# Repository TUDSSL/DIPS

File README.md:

# DIPS

This is the official public repository for **DIPS**: **D**ebugger for **I**ntermittently-**P**owered **S**ystems. The repository consists of all components that make DIPS:
- [Hardware](https://github.com/TUDSSL/DIPS/tree/master/hardware)
- [Debugger Firmware](https://github.com/TUDSSL/DIPS/tree/master/int-debugger-firmware)
- [Emulator Firmware](https://github.com/TUDSSL/DIPS/tree/master/int-debugger-emulator)
- [Emulator Host (GUI)](https://github.com/TUDSSL/DIPS/tree/master/int-debugger-emulator-host)
- [DIPS Console](https://github.com/TUDSSL/DIPS/tree/master/int-debugger-console)

## Project Overview
### Rationale
Intermittently-Powered or Battery-Free systems are low-powered embedded systems that experience frequent power failures. In recent years intermittently-powered systems have been explored excessively by the research community, but there was no good way of debugging these systems. DIPS aims to address this challenge. 

### Debugging Intermittently-Powered Systems
Common debuggers, like the [J-link](https://www.segger.com/products/debug-probes/j-link/), are perfect for debugging continuously-powered systems but will lose connection on a power failure when debugging intermittently-powered systems, making it useless for debugging battery-free systems. On top of that, intermittently-powered systems come with their own set of challenges by introducing new architectures like checkpointing. DIPS allows for continuous debugging despite power failures by reconnecting automatically and restoring the debugging state (Breakpoints) to the device under test. Scripts supplement the functionality of DIPS, allowing for automated tests of memory and peripheral consistency.

### Features:
DIPS integrates a fully featured emulator with close integration with an onboard hardware debugger. It can power devices under test through various modes and features current measurement capability. A key feature is the ability to pause emulation during debugger interaction, such as breakpoints. The emulator supports the following modes:
- Constant Voltage
- Sawtooth
- Square
- Triangle
- Virtual Buck-Boost (Allows for replaying energy harvesting traces to the device under test)
- Passive mode (Only takes over powering the device when prompted during debugging, requires passive debugging mode **mon passive_mode enable**)

The hardware debugger supports, through the associated console application, supports the following features:

- **energy_guards** energy-neutral code sections  where the emulator pauses
- **energy_breakpoints** that only trigger if the voltage is lower than the specified threshold
- **dips_mem_check** memory state consistency verification script, configured in **dips_testing.json**
- **dips_peripheral_check** peripheral state consistency verification script, configured in **dips_testing.json**
- Printing (**DIPS_PRINTF**), asserts (**DIPS_ASSERT**) and manually attaching (**DIPS_ATTACH**) through a simple C interface
- Passive operation (**wait_connect**) where the debugger only connects when prompted through a pin. 

### Hardware

#### Hardware Debugger
The hardware design of the debugger centers around a STM32F103RET MCU (A) and is based on the [Black Magic Debug Probe](https://github.com/blackmagic-debug/blackmagic). It is able to communicate with the energy emulator through SPI. The MCU interfaces with the DUT through SWD/JTAG or SBW (E), I/O interrupt pins and acts as a UART-USB bridge (D). To translate the signals to the DUT voltage, first, the DUT voltage is buffered using a low input bias current buffer amplifier OPA192. Next, all the interfaces with the DUT are level shifted by level translators (C) using the buffered DUT
voltage. The debugger connects to the PC with USB (B). 

#### Energy Emulator 
Central to the energy emulator is the low-noise TPS7A87 (I) linear regulator. The regulator generates the adjustable supply rail to the DUT (J). Power consumption by the DUT is measured by two INA186 current sense amplifiers (H). The first amplifier with a 5.6 Ω sense resistor measures large currents without imposing a high burden voltage. The second amplifier with a 1000 Ω sense resistor measures low currents and is able to be bypassed at large currents preventing high burden voltages. Two analog switches allow for quickly disabling the output and discharging the output through a 47 Ω resistor. The emulator is controlled by a STM32F373 MCU (G). With its on-board DAC DIPS is able to adjust the linear regulator and samples the output voltage and the output of the current sense amplifiers (each using one of its dedicated on-board Sigma Delta ADCs). The energy emulator connects to the PC with USB (F)

#### Design files
In the **hardware** folder both the KICAD design files are provided together with a PDF schematic and gerbers.

## Getting Started
This repository has all information to build your own DIPS. Below we describe building and executing the complete repository of DIPS, including hardware, debugger software, emulator software and both emulator and console applications.

### Building the Debugger Firmware
The hardware debugger firmware is based on the [Black Magic Probe](https://github.com/blackmagic-debug/blackmagic) and can be found in the [/int-debugger-firmware](https://github.com/TUDSSL/DIPS/tree/master/int-debugger-firmware) folder

#### Build Process
After cloning the repository one can compile the firmware in two ways, first is by running it as a [PlatformIO](https://platformio.org/) project or by building it from scratch using the provided cmake files running the following section:

```
$ cd int-debugger-firmware
$ pio run
```

After building, you can upload the firmware to the MCU using your favourite flashing method whilst powering the platform using USB.

#### Last Tested Software Versions
This software was build successfully with these software versions:

- CMake version 3.26.3 
- arm-none-eabi-gcc version 13.1.0 
- arm-none-eabi-newlib version 4.3.0.20230120
- arm-none-eabi-binutils version 2.40 
- PlatformIO version 6.1.7

### The Emulator Firmware
The emulator firmware is located in the [/int-debugger-emulator](https://github.com/TUDSSL/DIPS/tree/master/int-debugger-emulator) folder

#### Build Process
After cloning the repository the emulator can be compiled and build by running the enclosed cmake commands:

```
$ cd int-debugger-emulator
$ mkdir build
$ cd build
$ cmake ..
$ make
```

After building, you can upload the firmware to the MCU using your favourite flashing method whilst powering the platform using USB.

#### Note on the Emulator Firmware
The firmware is based upon the [FreeRTOS](https://www.freertos.org/) framework, allowing real-time switching of tasks required for the emulator.

#### Last Tested Software Versions
This software was build successfully with these software versions:

- CMake version 3.26.3 
- arm-none-eabi-gcc version 13.1.0 
- arm-none-eabi-newlib version 4.3.0.20230120
- arm-none-eabi-binutils version 2.40
- Protobuf version 21.12

### Building the Emulator Host Software
The next part of software runs on the host PC and is used for communicating with the hardware emulator. The sofware can be found in the [/int-debugger-emulator-host](https://github.com/TUDSSL/DIPS/tree/master/int-debugger-emulator-host) folder.

#### Build Process
After cloning the repository the emulator host application can be compiled and build by running the following commands:

```
$ cd int-debugger-emulator-host
$ cmake .
$ make
```

#### Last Tested Software Versions
This software was build successfully with these software versions:

- [QT](https://www.qt.io/) version 5.15.9
- [HighFive](https://github.com/BlueBrain/HighFive) commit 00dad7172c
- Protobuf version 21.12
- HDF5 version 1.14.1

### The DIPS Console Software
The next part of software also runs on the host PC and is used as a GDB wrapper, allowing the added features of DIPS. The sofware can be found in the [/int-debugger-console](https://github.com/TUDSSL/DIPS/tree/master/int-debugger-console) folder.

#### Setup
Since the DIPS console is a python executable, there is no need for compilation. Install the python libraries mentioned in the `requirements.txt` file and you should be good to go.

#### Last Tested Software Versions
This software was build successfully with these software versions:

- Python version 3.11.3
- Python-pyGDBmi version 0.11.0.0
- Python-pyserial version 3.5
- Python-prompt_toolkit version 3.0.38 
- Python-cmsis_svd version 0.4

#### Execute DIPS Console Application
The DIPS console application can be started by calling the `python3 main.py`, if you have an elf-file binary, you can load this by adding this as extra parameter `python3 main.py firmware.elf`. Other GDB parameters and queries from the command line are avaliable as well.

##### Connecting to DIPS
If you have your DIPS connected over USB you can connect to the hardware by running the `connect` command. The console will automatically search for a DIPS serial connection, establish this connection and connect to the attached device under test. Now one can start debugging intermittenlty-powered systems with DIPS, just like debugging regular powered embedded systems. Manual connection to DIPS is also possible by running the following sequence:

```
(gdb) tar ext /dev/ttyACM0
(gdb) mon s
(gdb) attach 1
```

##### Sample session
After connecting to the DIPS and the device under test, regular arm-none-eabi-gdb commands are availble for use:

```
> python3 main.py example.elf
...<GDB Copyright message>
(gdb) connect
Remote debugging using /dev/ttyACM0
Target voltage: 3.00V
Available Targets:
No. Att Driver
 1      STM32F40x M3/M4
Attaching to program: <code_folder>/example.elf, Remote target
0x800007c in main ()
(gdb) load
Loading section .text, size 0x5868 lma 0x8000000
Loading section .data, size 0x9e0 lma 0x8005868
Loading section .rodata, size 0x254 lma 0x8006248
Start address 0x800007c, load size 25756
Transfer rate: 31 KB/sec, 919 bytes/write.
(gdb) b main
(gdb) c
Breakpoint 1 at 0x80000e8: file <code_folder>/main.c, line 20.
(gdb)
```
## How to Cite This Work

The results of this project have been published in a peer-reviewed academic publication (from which all technical figures in this file originate). Details of the publication are as follows.

* **Authors and the project team:** [Jasper de Winkel](https://www.jasperdewinkel.com/), [Tom Hoefnagel](https://www.linkedin.com/in/tobrec), [Boris Blokland](https://www.linkedin.com/in/boris-blokland-2a0b22138/), [Przemysław Pawełczak](https://www.pawelczak.net/)
* **Publication title:** _DIPS: Debug Intermittently-Powered Systems Like Any Embedded System_
* **Pulication venue:** [Proceedings of ACM SenSys 2022](http://sensys.acm.org/2022/)
* [**Link to publication**](https://doi.org/10.1145/3560905.3568543)

To cite this publication please use the following BiBTeX entry.

```
@inproceedings{dewinkel:sensys:2022:dips,
 author = {de Winkel, Jasper and Hoefnagel, Tom and Blokland, Boris and Pawe\l{}czak, Przemys\l{}aw},
 title = {{DIPS}: Debug Intermittently-Powered Systems Like Any Embedded System},
 booktitle = {Proc. SenSys},
 year = {2022},
 address = {Boston, MA, USA},
 date = nov # " 6--9",
 publisher = {ACM},
 url = {https://doi.org/10.1145/3560905.3568543}
}
```

## Acknowledgments

This research project was supported by [Netherlands Organisation for Scientific Research](https://www.nwo.nl/en), partly funded by the [Dutch Ministry of Economic Affairs and Climate Policy](https://www.government.nl/ministries/ministry-of-economic-affairs-and-climate-policy), through [TTW Perspective program ZERO (P15-01)](https://www.nwo.nl/en/researchprogrammes/perspectief/previous-awards/zero-towards-energy-autonomous-systems-iot) within Project P1.

## Copyright

Copyright (C) 2022 TU Delft Embedded Systems Group/Sustainable Systems Laboratory.

MIT Licence or otherwise specified. See [license](https://github.com/TUDSSL/ENGAGE/blob/master/LICENSE) file for details.

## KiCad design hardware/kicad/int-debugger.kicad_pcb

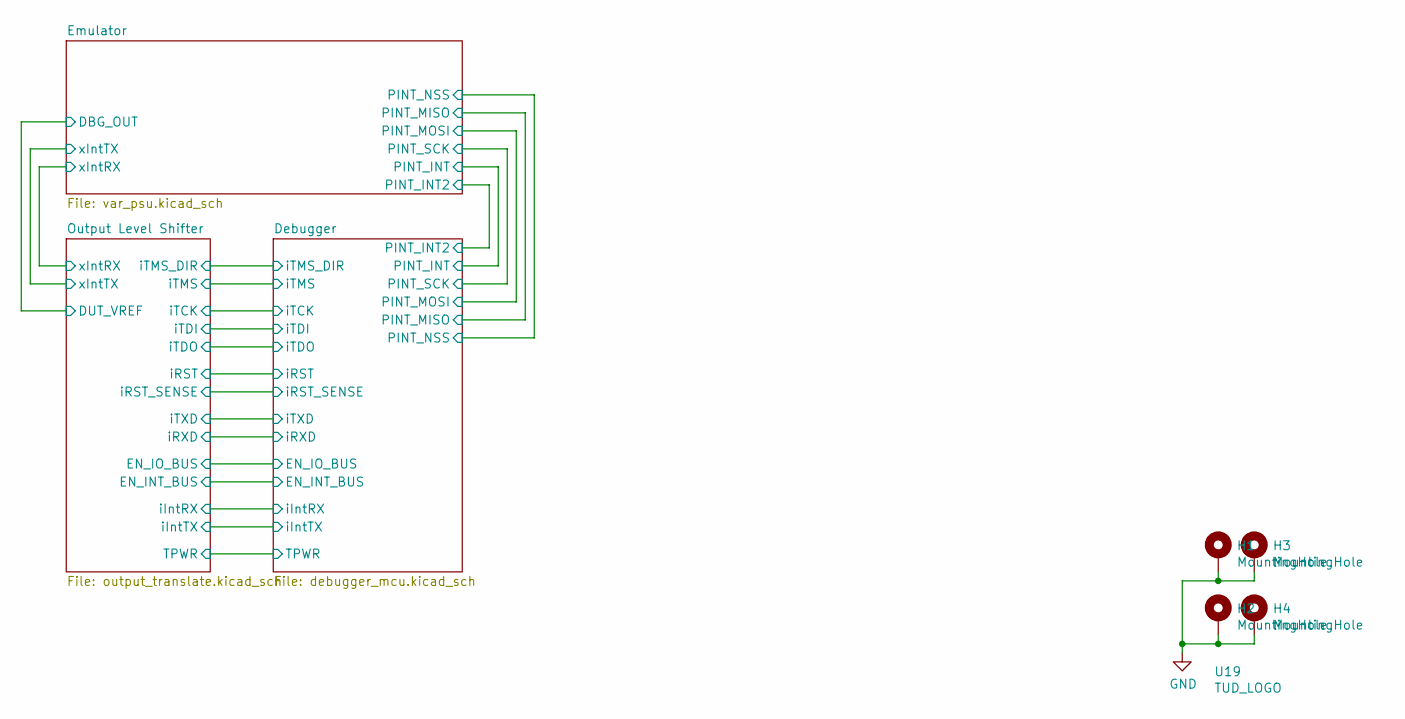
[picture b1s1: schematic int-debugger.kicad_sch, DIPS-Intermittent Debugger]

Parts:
H1, H2, H3, H4: MountingHole; MountingHole_2.2mm_M2_DIN965_Pad_TopBottom
U19: TUD_LOGO; DELFT_LOGO2

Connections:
GND: H1.1, H2.1, H3.1, H4.1; also elsewhere on the board

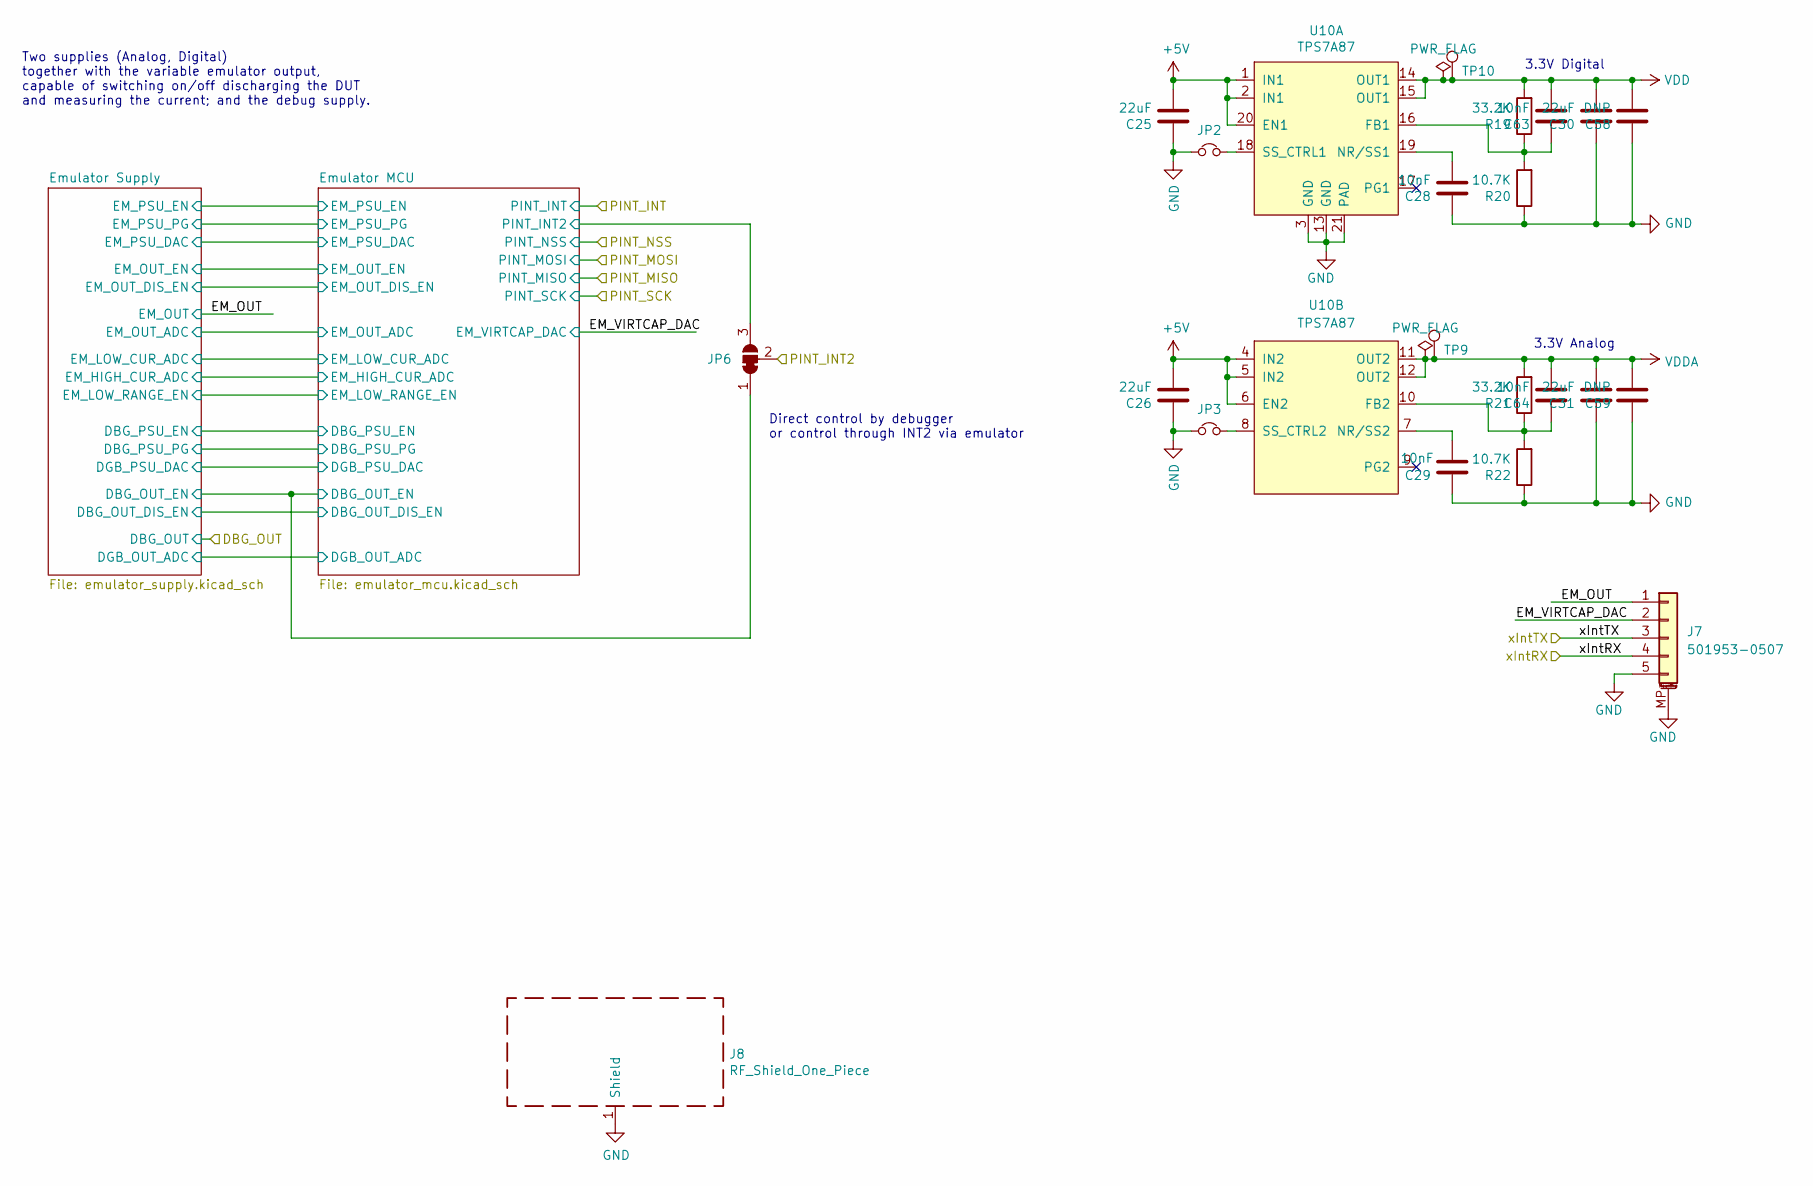
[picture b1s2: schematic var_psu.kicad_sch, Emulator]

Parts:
C25, C26, C30, C31: 22uF; C_0603_1608Metric; MPN GRM188R61A226ME15D
C28, C29, C63, C64: 10nF; C_0603_1608Metric; MPN 06035C103KAT2A
C58, C59: DNP; C_0603_1608Metric
J7: 501953-0507; Molex_Pico-Clasp_501953-0507_1x05-1MP_P1.00mm_Horizontal; MPN 501953-0507
J8: RF_Shield_One_Piece; Laird_Technologies_BMI-S-209-F_29.36x18.50mm; MPN BMI-S-209-F + BMI-S-209-C
JP2, JP3: Jumper_NC_Small; SolderJumper-small-nc
JP6: SolderJumper_3_Bridged12; SolderJumper-3_P1.3mm_Bridged12_Pad1.0x1.5mm
R19, R21: 33.2K; R_0603_1608Metric; MPN RC0603FR-0733K2L
R20, R22: 10.7K; R_0603_1608Metric; MPN RC0603FR-0710K7L
TP9, TP10: TestPoint; TestPoint_Keystone_5000-5004_Miniature
U10: TPS7A87; Texas-WQFN-20

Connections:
+5V: C25.2, C26.2, U10.1 (IN1), U10.2 (IN1), U10.4 (IN2), U10.5 (IN2), U10.6 (EN2), U10.20 (EN1); also elsewhere on the board
/Debugger/PINT_INT2: JP6.2 (C); also elsewhere on the board
/Emulator/EM_OUT: J7.1; also elsewhere on the board
/Emulator/EM_VIRTCAP_DAC: J7.2; also elsewhere on the board
/Emulator/Emulator MCU/DBG_OUT_EN: JP6.1 (A); also elsewhere on the board
/Emulator/Emulator MCU/PINT_INT2: JP6.3 (B); also elsewhere on the board
/Emulator/xIntRX: J7.4; also elsewhere on the board
/Emulator/xIntTX: J7.3; also elsewhere on the board
GND: C25.1, C26.1, C28.1, C29.1, C30.1, C31.1, C58.1, C59.1, J7.5, J7.MP (MountPin), J8.1 (Shield), JP2.1, JP3.1, R20.1, R22.1, U10.3 (GND), U10.13 (GND), U10.21 (PAD); also elsewhere on the board
unnamed: C63.1, R19.1, R20.2, U10.16 (FB1)
unnamed: C28.2, U10.19 (NR/SS1)
unnamed: JP2.2, U10.18 (SS_CTRL1)
unnamed: C64.1, R21.1, R22.2, U10.10 (FB2)
unnamed: C29.2, U10.7 (NR/SS2)
unnamed: JP3.2, U10.8 (SS_CTRL2)
VDD: C30.2, C58.2, C63.2, R19.2, TP10.1, U10.14 (OUT1), U10.15 (OUT1); also elsewhere on the board
VDDA: C31.2, C59.2, C64.2, R21.2, TP9.1, U10.11 (OUT2), U10.12 (OUT2); also elsewhere on the board

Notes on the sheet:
Direct control by debugger or control through INT2 via emulator
3.3V Digital
Two supplies (Analog, Digital) together with the variable emulator output, capable of switching on/off discharging the DUT and measuring the current; and the debug supply.
3.3V Analog

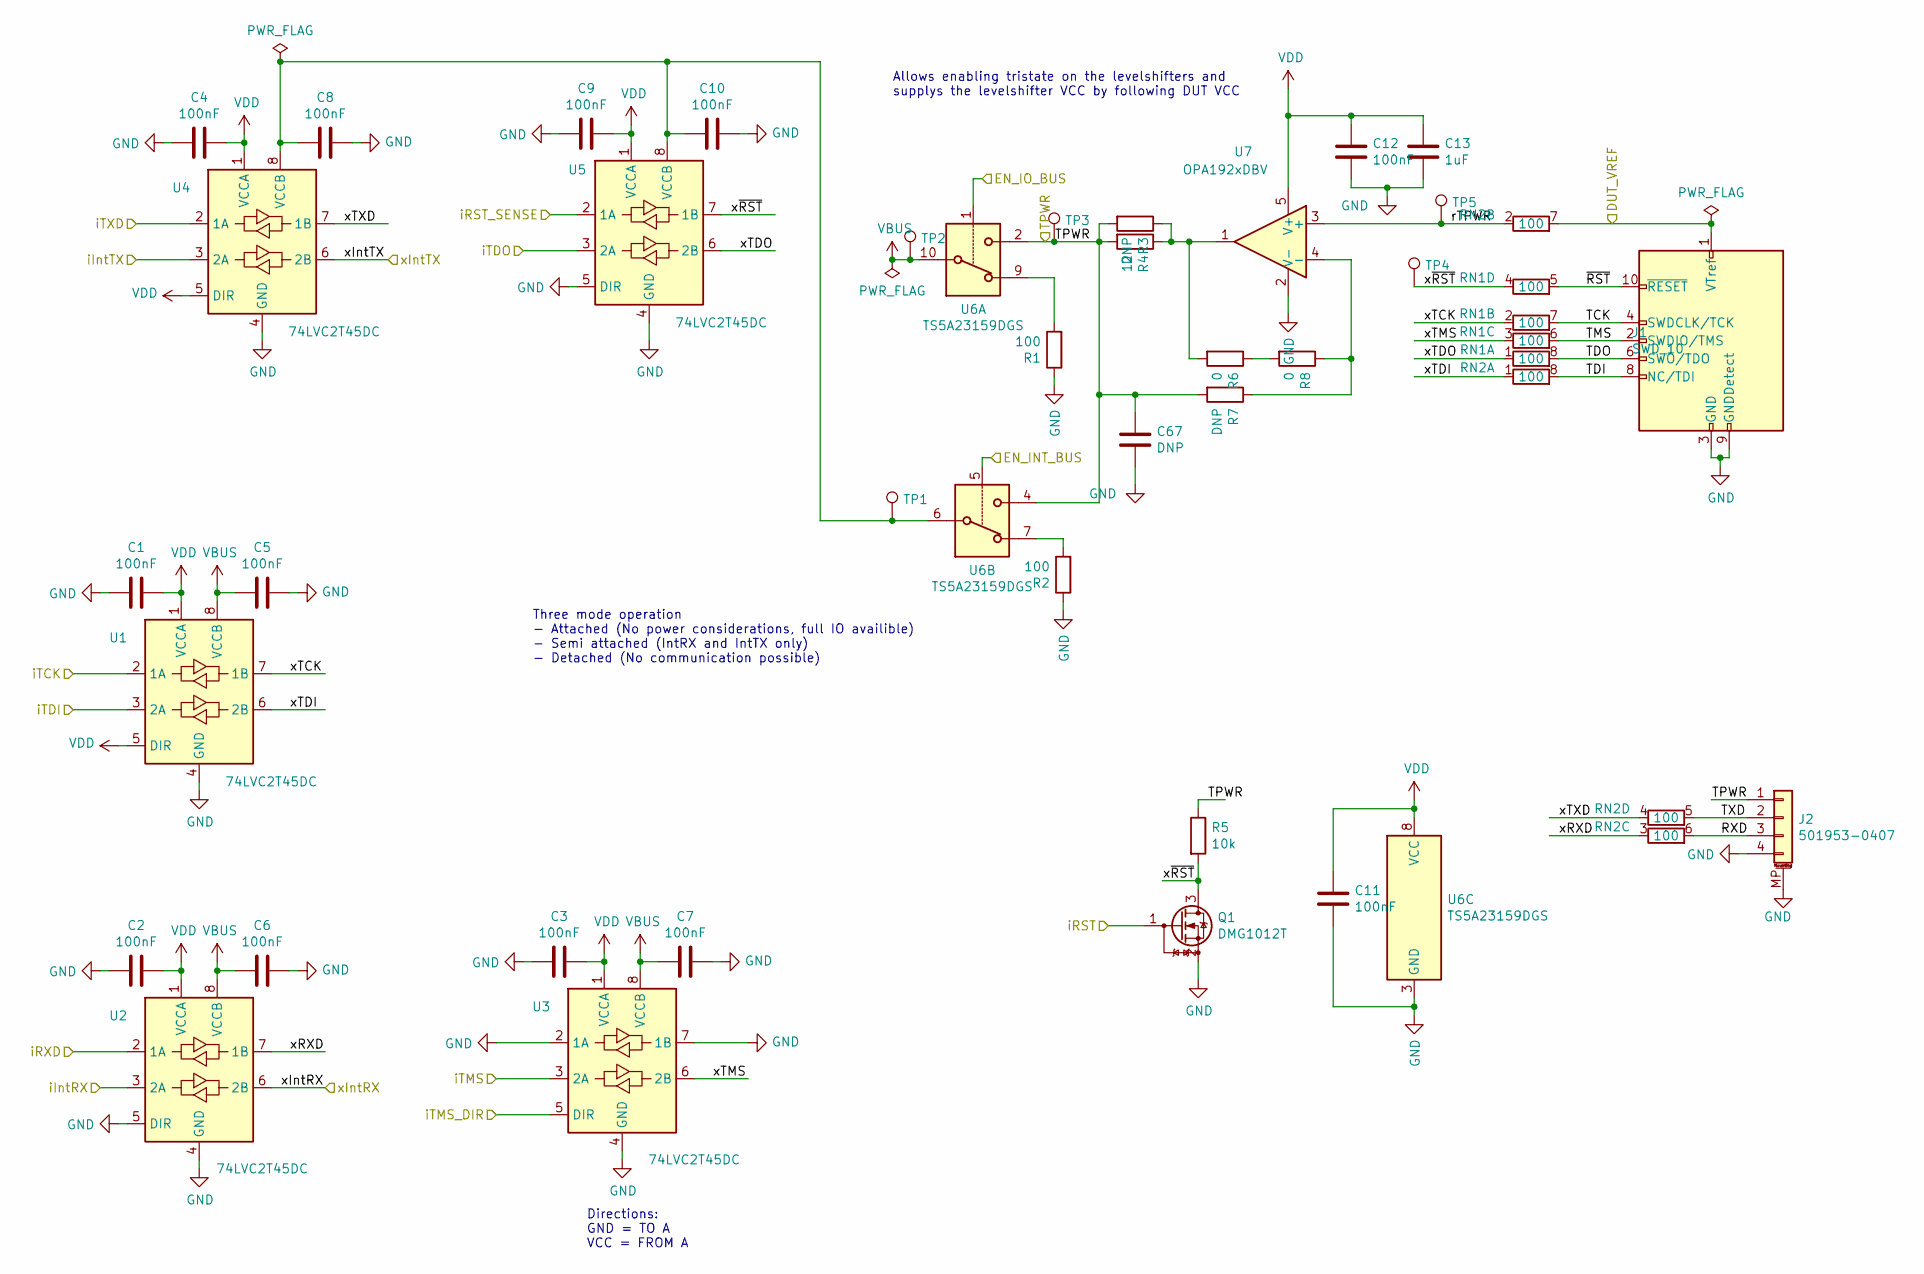
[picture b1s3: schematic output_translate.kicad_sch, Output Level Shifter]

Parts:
C1, C2, C3, C4, C5, C6, C7, C8, C9, C10, C11, C12: 100nF; C_0603_1608Metric; MPN CL10B104KB8NNNC
C13: 1uF; C_0603_1608Metric; MPN TMK107B7105KA-T
C67: DNP; C_0603_1608Metric
J1: SWD_10; FTSH-105-01-F-D-RA-K; MPN FTSH-105-01-F-D-RA-K
J2: 501953-0407; Molex_Pico-Clasp_501953-0407_1x04-1MP_P1.00mm_Horizontal; MPN 501953-0407
Q1: DMG1012T; SOT-523; MPN DMG1012T
R1, R2: 100; R_0603_1608Metric; MPN RC0603FR-07100RL
R3, R7: DNP; R_0603_1608Metric
R4: 12; R_0603_1608Metric; MPN RC0603FR-0712RL
R5: 10k; R_0603_1608Metric; MPN RC0603FR-0710KL
R6, R8: 0; R_0603_1608Metric; MPN RC0603FR-070RL
RN1, RN2: 100; R_Array_Convex_4x1206; MPN YC324-JK-07100RL
TP1, TP2, TP3, TP4, TP5: TestPoint; TestPoint_Keystone_5000-5004_Miniature
U1, U2, U3, U4, U5: 74LVC2T45DC; VSSOP-8_2.3x2mm_P0.5mm; MPN 74LVC2T45DC
U6: TS5A23159DGS; VSSOP-10_3x3mm_P0.5mm; MPN TS5A23159DGS
U7: OPA192xDBV; SOT-23-5; MPN OPA192IDBV

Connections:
/Debugger/EN_INT_BUS: U6.5; also elsewhere on the board
/Debugger/EN_IO_BUS: U6.1; also elsewhere on the board
/Debugger/TPWR: C67.1, J2.1, R3.2, R4.2, R5.1, R7.2, TP3.1, U6.2, U6.4; also elsewhere on the board
/Debugger/iIntRX: U2.3 (2A); also elsewhere on the board
/Debugger/iIntTX: U4.3 (2A); also elsewhere on the board
/Debugger/iRST: Q1.1 (G); also elsewhere on the board
/Debugger/iRST_SENSE: U5.2 (1A); also elsewhere on the board
/Debugger/iRXD: U2.2 (1A); also elsewhere on the board
/Debugger/iTCK: U1.2 (1A); also elsewhere on the board
/Debugger/iTDI: U1.3 (2A); also elsewhere on the board
/Debugger/iTDO: U5.3 (2A); also elsewhere on the board
/Debugger/iTMS: U3.3 (2A); also elsewhere on the board
/Debugger/iTMS_DIR: U3.5 (DIR); also elsewhere on the board
/Debugger/iTXD: U4.2 (1A); also elsewhere on the board
/Emulator/DBG_OUT: J1.1 (VTref), RN2.7 (R2.2); also elsewhere on the board
/Emulator/xIntRX: U2.6 (2B); also elsewhere on the board
/Emulator/xIntTX: U4.6 (2B); also elsewhere on the board
/Output Level Shifter/RXD: J2.3, RN2.6 (R3.2)
/Output Level Shifter/TCK: J1.4 (SWDCLK/TCK), RN1.7 (R2.2)
/Output Level Shifter/TDI: J1.8 (NC/TDI), RN2.8 (R1.2)
/Output Level Shifter/TDO: J1.6 (SWO/TDO), RN1.8 (R1.2)
/Output Level Shifter/TMS: J1.2 (SWDIO/TMS), RN1.6 (R3.2)
/Output Level Shifter/TXD: J2.2, RN2.5 (R4.2)
/Output Level Shifter/rTPWR: RN2.2 (R2.1), TP5.1, U7.3 (+)
/Output Level Shifter/xRXD: RN2.3 (R3.1), U2.7 (1B)
/Output Level Shifter/xTCK: RN1.2 (R2.1), U1.7 (1B)
/Output Level Shifter/xTDI: RN2.1 (R1.1), U1.6 (2B)
/Output Level Shifter/xTDO: RN1.1 (R1.1), U5.6 (2B)
/Output Level Shifter/xTMS: RN1.3 (R3.1), U3.6 (2B)
/Output Level Shifter/xTXD: RN2.4 (R4.1), U4.7 (1B)
/Output Level Shifter/x~RST: Q1.3 (D), R5.2, RN1.4 (R4.1), TP4.1, U5.7 (1B)
/Output Level Shifter/~RST: J1.10 (~RESET), RN1.5 (R4.2)
GND: C1.2, C2.2, C3.2, C4.2, C5.1, C6.1, C7.1, C8.1, C9.2, C10.1, C11.2, C12.2, C13.2, C67.2, J1.3 (GND), J1.5 (GND), J1.9 (GNDDetect), J2.4, J2.MP (MountPin), Q1.2 (S), R1.1, R2.1, U1.4 (GND), U2.4 (GND), U2.5 (DIR), U3.2 (1A), U3.4 (GND), U3.7 (1B), U4.4 (GND), U5.4 (GND), U5.5 (DIR), U6.3 (GND), U7.2 (V-); also elsewhere on the board
unnamed: R1.2, U6.9
unnamed: R2.2, U6.7
unnamed: R3.1, R4.1, R6.2, U7.1
unnamed: R6.1, R8.2
unnamed: C8.2, C10.2, TP1.1, U4.8 (VCCB), U5.8 (VCCB), U6.6
unnamed: R7.1, R8.1, U7.4 (-)
VBUS: C5.2, C6.2, C7.2, TP2.1, U1.8 (VCCB), U2.8 (VCCB), U3.8 (VCCB), U6.10
VDD: C1.1, C2.1, C3.1, C4.1, C9.1, C11.1, C12.1, C13.1, U1.1 (VCCA), U1.5 (DIR), U2.1 (VCCA), U3.1 (VCCA), U4.1 (VCCA), U4.5 (DIR), U5.1 (VCCA), U6.8 (VCC), U7.5 (V+); also elsewhere on the board

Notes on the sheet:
Allows enabling tristate on the levelshifters and supplys the levelshifter VCC by following DUT VCC
Three mode operation - Attached (No power considerations, full IO availible) - Semi attached (IntRX and IntTX only) - Detached (No communication possible)
Directions: GND = TO A VCC = FROM A

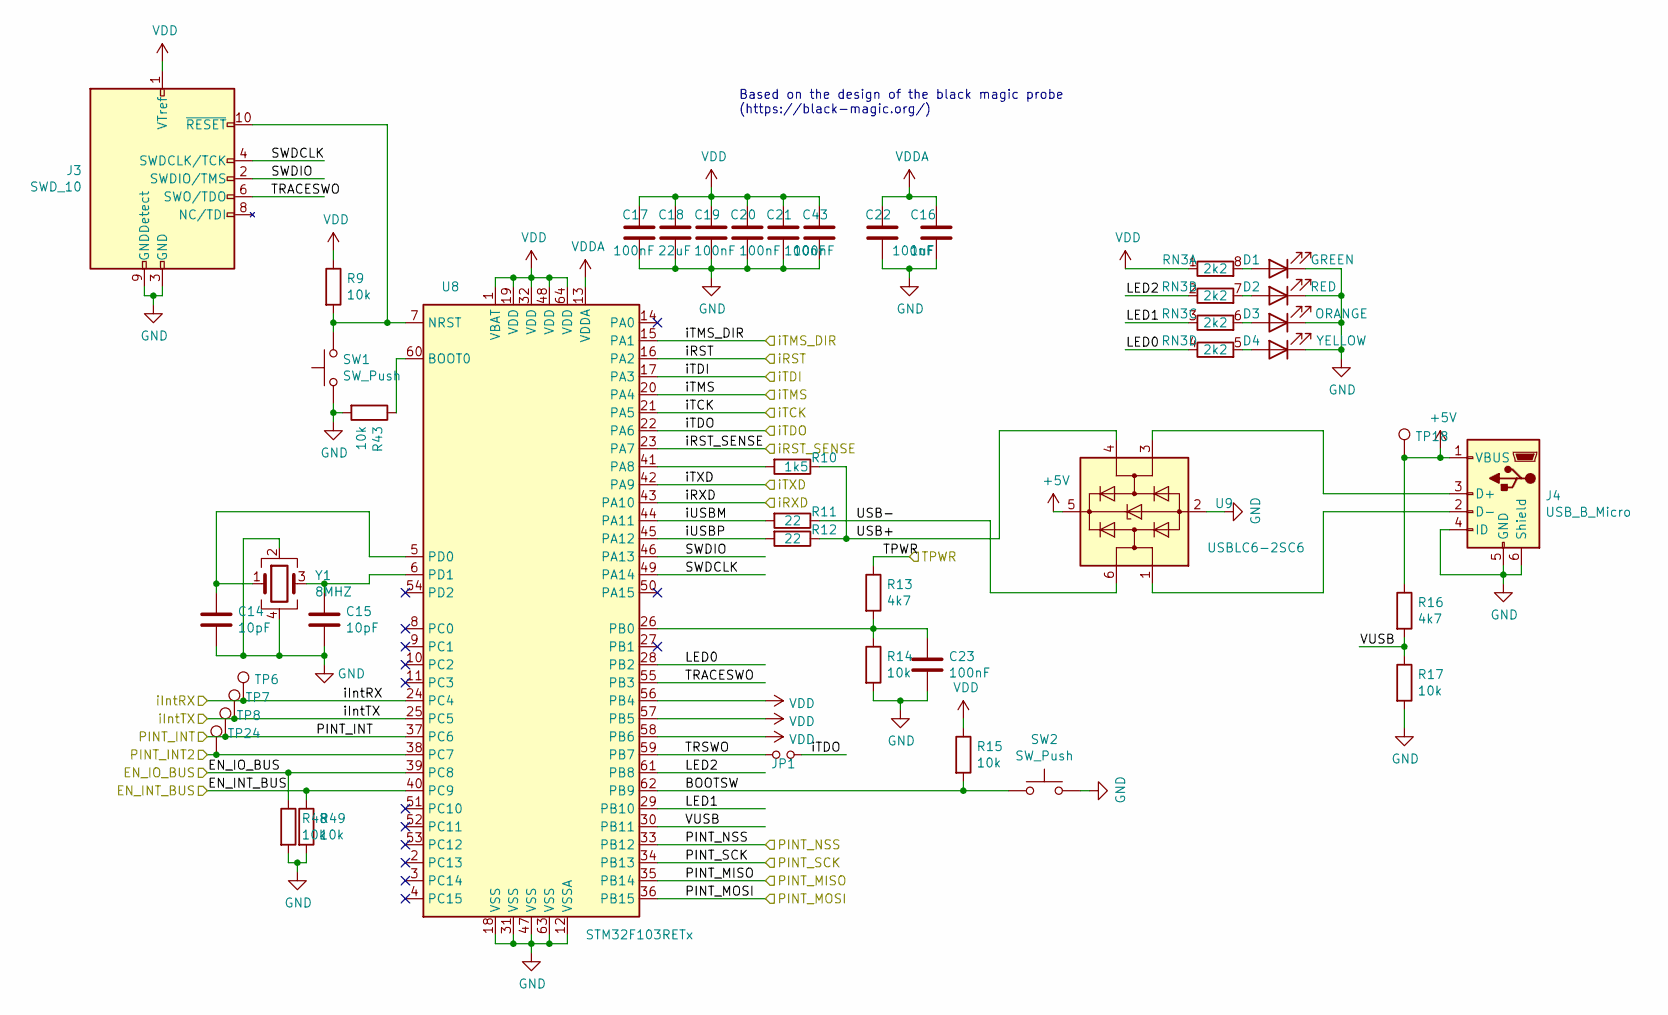
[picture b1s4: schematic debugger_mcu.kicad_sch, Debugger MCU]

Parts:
C14, C15: 10pF; C_0603_1608Metric; MPN CC0603CRNPO9BN100
C16: 1uF; C_0603_1608Metric; MPN TMK107B7105KA-T
C17, C19, C20, C21, C22, C23, C43: 100nF; C_0603_1608Metric; MPN CL10B104KB8NNNC
C18: 22uF; C_0603_1608Metric; MPN GRM188R61A226ME15D
D1: GREEN; LED_0603_1608Metric; MPN LTST-C190KGKT
D2: RED; LED_0603_1608Metric; MPN LTST-C193KRKT-5A
D3: ORANGE; LED_0603_1608Metric; MPN APT1608LSECK/J4-PRV
D4: YELLOW; LED_0603_1608Metric; MPN APTD1608LSYCK/J3-PF
J3: SWD_10; ftsh-105-01-f-dv-k; MPN ftsh-105-01-f-dv-k
J4: USB_B_Micro; USB_Micro-B_Molex-105017-0001; MPN 105017-0001
JP1: Jumper_NO_Small; SolderJumper-small-no-150um
R9, R14, R15, R17, R43, R48, R49: 10k; R_0603_1608Metric; MPN RC0603FR-0710KL
R10: 1k5; R_0603_1608Metric; MPN RC0603FR-071K5L
R11, R12: 22; R_0603_1608Metric; MPN RC0603FR-0722RL
R13, R16: 4k7; R_0603_1608Metric; MPN RC0603FR-074K7L
RN3: 2k2; R_Array_Convex_4x1206; MPN YC324-JK-072K2L
SW1, SW2: SW_Push; SW_SPST_B3U-1000P; MPN B3U-1000P
TP6, TP7, TP8, TP18, TP24: TestPoint; TestPoint_Keystone_5000-5004_Miniature
U8: STM32F103RETx; LQFP-64_10x10mm_P0.5mm; MPN STM32F103RET
U9: USBLC6-2SC6; SOT-23-6; MPN USBLC6-2SC6
Y1: 8MHZ; Crystal_SMD_Abracon_ABM3B-4Pin_5.0x3.2mm; MPN ABM3B-8.000MHZ-10-D-1-G-T

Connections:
+5V: J4.1 (VBUS), R16.1, TP18.1, U9.5 (VBUS); also elsewhere on the board
/Debugger/BOOTSW: R15.2, SW2.1, U8.62 (PB9)
/Debugger/EN_INT_BUS: R49.1, U8.40 (PC9); also elsewhere on the board
/Debugger/EN_IO_BUS: R48.1, U8.39 (PC8); also elsewhere on the board
/Debugger/LED0: RN3.4 (R4.1), U8.28 (PB2)
/Debugger/LED1: RN3.3 (R3.1), U8.29 (PB10)
/Debugger/LED2: RN3.2 (R2.1), U8.61 (PB8)
/Debugger/PINT_INT: TP8.1, U8.37 (PC6); also elsewhere on the board
/Debugger/PINT_INT2: TP24.1, U8.38 (PC7); also elsewhere on the board
/Debugger/PINT_MISO: U8.35 (PB14); also elsewhere on the board
/Debugger/PINT_MOSI: U8.36 (PB15); also elsewhere on the board
/Debugger/PINT_NSS: U8.33 (PB12); also elsewhere on the board
/Debugger/PINT_SCK: U8.34 (PB13); also elsewhere on the board
/Debugger/SWDCLK: J3.4 (SWDCLK/TCK), U8.49 (PA14)
/Debugger/SWDIO: J3.2 (SWDIO/TMS), U8.46 (PA13)
/Debugger/TPWR: R13.1; also elsewhere on the board
/Debugger/TRACESWO: J3.6 (SWO/TDO), U8.55 (PB3)
/Debugger/TRSWO: JP1.1, U8.59 (PB7)
/Debugger/USB+: R10.1, R12.1, U9.4 (I/O2)
/Debugger/USB-: R11.1, U9.6 (I/O1)
/Debugger/VUSB: R16.2, R17.1, U8.30 (PB11)
/Debugger/iIntRX: TP6.1, U8.24 (PC4); also elsewhere on the board
/Debugger/iIntTX: TP7.1, U8.25 (PC5); also elsewhere on the board
/Debugger/iRST: U8.16 (PA2); also elsewhere on the board
/Debugger/iRST_SENSE: U8.23 (PA7); also elsewhere on the board
/Debugger/iRXD: U8.43 (PA10); also elsewhere on the board
/Debugger/iTCK: U8.21 (PA5); also elsewhere on the board
/Debugger/iTDI: U8.17 (PA3); also elsewhere on the board
/Debugger/iTDO: JP1.2, U8.22 (PA6); also elsewhere on the board
/Debugger/iTMS: U8.20 (PA4); also elsewhere on the board
/Debugger/iTMS_DIR: U8.15 (PA1); also elsewhere on the board
/Debugger/iTXD: U8.42 (PA9); also elsewhere on the board
/Debugger/iUSBM: R11.2, U8.44 (PA11)
/Debugger/iUSBP: R12.2, U8.45 (PA12)
GND: C14.2, C15.2, C16.2, C17.2, C18.2, C19.2, C20.2, C21.2, C22.2, C23.2, C43.2, D1.1 (K), D2.1 (K), D3.1 (K), D4.1 (K), J3.3 (GND), J3.5 (GND), J3.9 (GNDDetect), J4.4 (ID), J4.5 (GND), J4.6 (Shield), R14.2, R17.2, R43.2, R48.2, R49.2, SW1.1, SW2.2, U8.12 (VSSA), U8.18 (VSS), U8.31 (VSS), U8.47 (VSS), U8.63 (VSS), U9.2 (GND), Y1.2, Y1.4; also elsewhere on the board
unnamed: D1.2 (A), RN3.8 (R1.2)
unnamed: D2.2 (A), RN3.7 (R2.2)
unnamed: D3.2 (A), RN3.6 (R3.2)
unnamed: D4.2 (A), RN3.5 (R4.2)
unnamed: J3.10 (~RESET), R9.2, SW1.2, U8.7 (NRST)
unnamed: J4.3 (D+), U9.3 (I/O2)
unnamed: J4.2 (D-), U9.1 (I/O1)
unnamed: R43.1, U8.60 (BOOT0)
unnamed: R10.2, U8.41 (PA8)
unnamed: C23.1, R13.2, R14.1, U8.26 (PB0)
unnamed: C14.1, U8.5 (PD0), Y1.1
unnamed: C15.1, U8.6 (PD1), Y1.3
VDD: C17.1, C18.1, C19.1, C20.1, C21.1, C43.1, J3.1 (VTref), R9.1, R15.1, RN3.1 (R1.1), U8.1 (VBAT), U8.19 (VDD), U8.32 (VDD), U8.48 (VDD), U8.56 (PB4), U8.57 (PB5), U8.58 (PB6), U8.64 (VDD); also elsewhere on the board
VDDA: C16.1, C22.1, U8.13 (VDDA); also elsewhere on the board

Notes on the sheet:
Based on the design of the black magic probe (https://black-magic.org/)

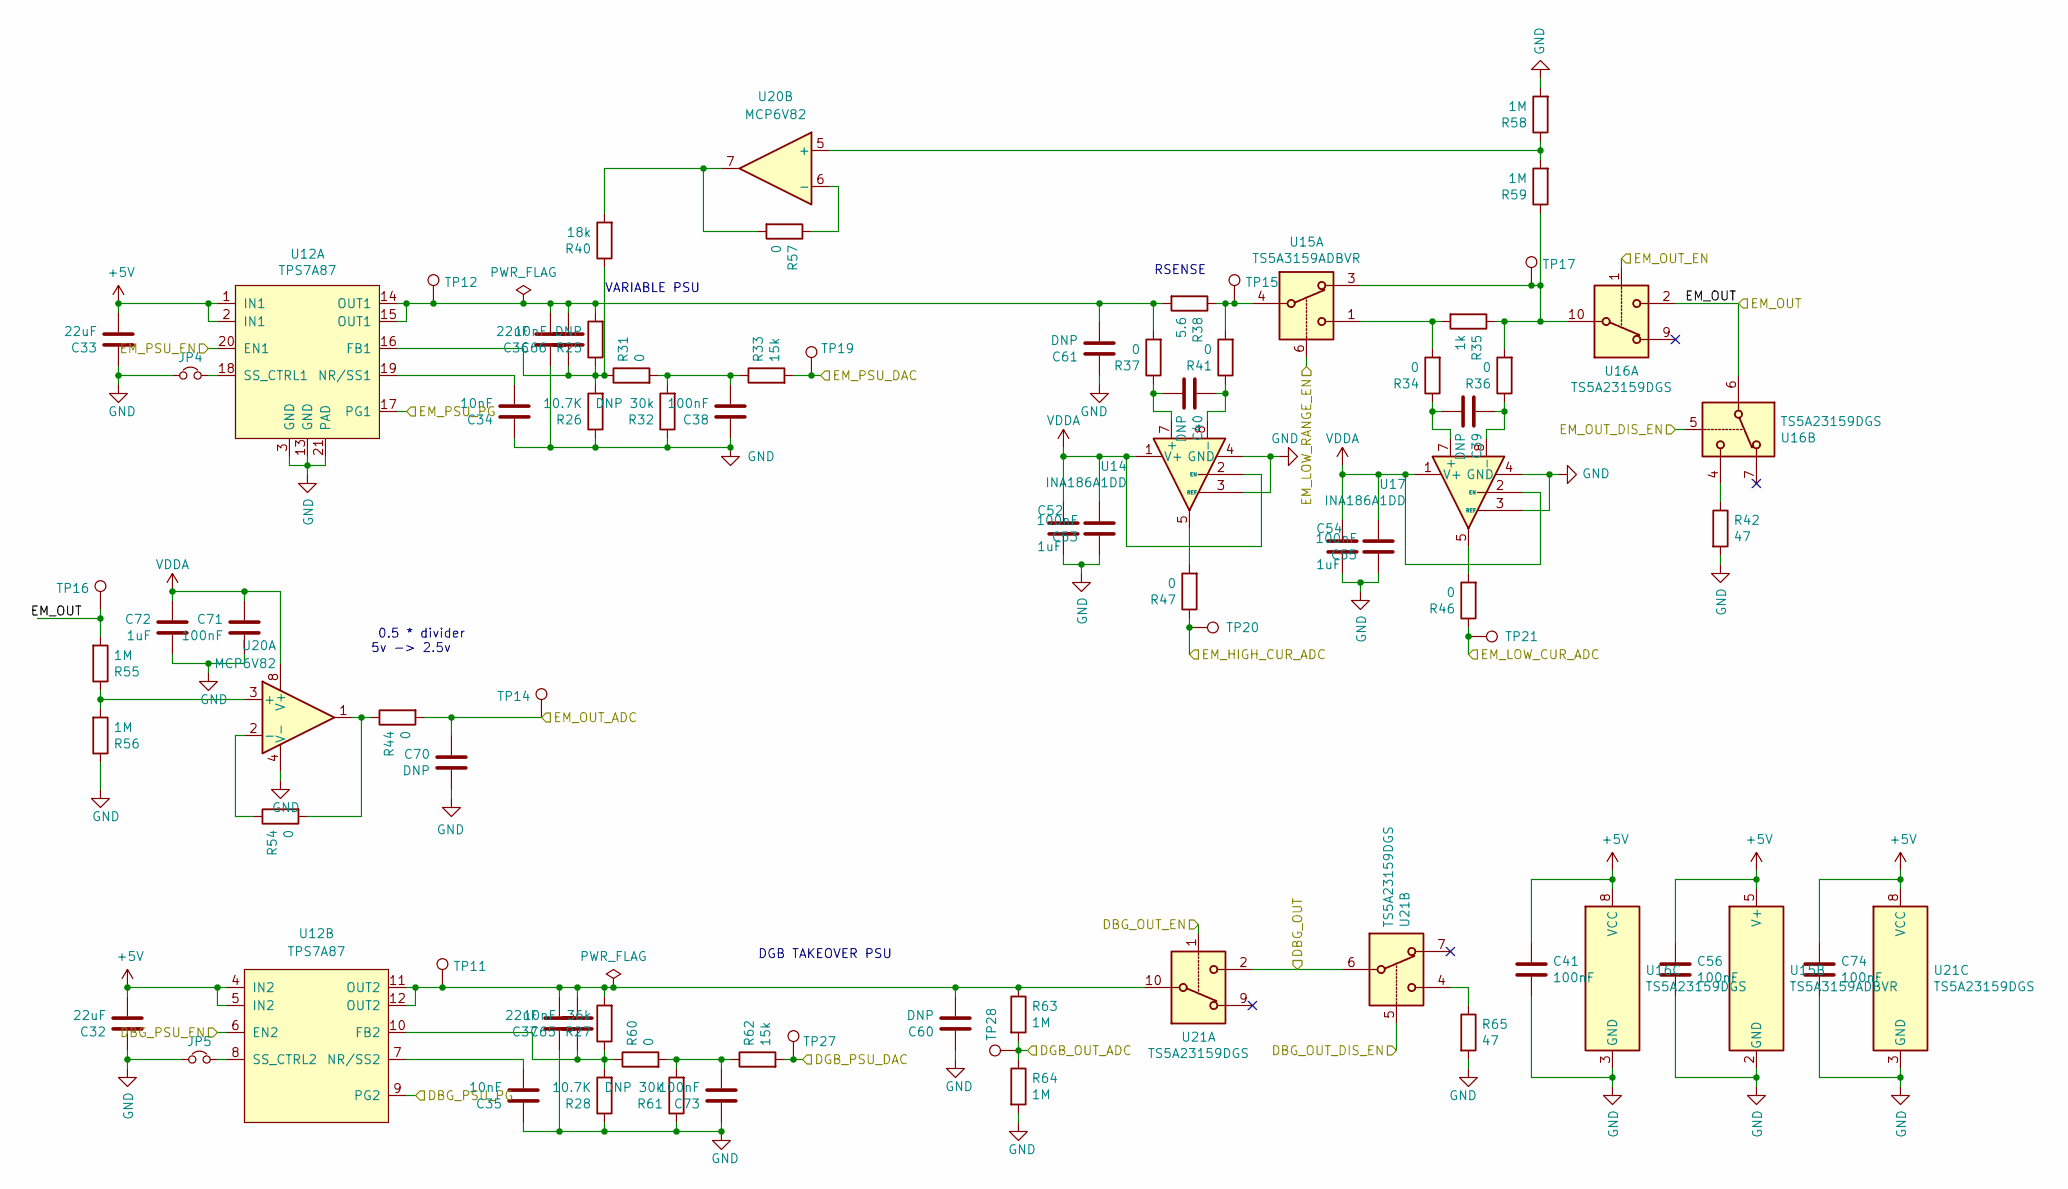
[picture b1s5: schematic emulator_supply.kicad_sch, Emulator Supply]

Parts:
C32, C33, C36, C37: 22uF; C_0603_1608Metric; MPN GRM188R61A226ME15D
C34, C35, C65, C66: 10nF; C_0603_1608Metric; MPN 06035C103KAT2A
C38, C41, C53, C55, C56, C71, C73, C74: 100nF; C_0603_1608Metric; MPN CL10B104KB8NNNC
C39, C40, C60, C61, C70: DNP; C_0603_1608Metric
C52, C54, C72: 1uF; C_0603_1608Metric; MPN TMK107B7105KA-T
JP4, JP5: Jumper_NC_Small; SolderJumper-small-nc
R25: DNP; R_0603_1608Metric
R26, R28: 10.7K; R_0603_1608Metric; MPN RC0603FR-0710K7L
R27: 36k; R_0603_1608Metric; MPN RC0603FR-0736KL
R31, R34, R36, R37, R41, R44, R46, R47, R54, R57, R60: 0; R_0603_1608Metric; MPN RC0603FR-070RL
R32, R61: DNP 30k; R_0603_1608Metric; MPN RC0603FR-0730KL
R33, R62: 15k; R_0603_1608Metric; MPN RC0603FR-0715KL
R35: 1k; R_0603_1608Metric; MPN MCWF06R1001BTL
R38: 5.6; R_0603_1608Metric; MPN ERJ3BQF5R6V
R40: 18k; R_0603_1608Metric; MPN RC0603FR-0718KL
R42, R65: 47; R_1206_3216Metric; MPN RC1206FR-7W47RL
R55, R56, R58, R59, R63, R64: 1M; R_0603_1608Metric; MPN MC008457
TP11, TP12, TP15, TP16, TP17: TestPoint; TestPoint_Keystone_5000-5004_Miniature
TP14, TP19, TP20, TP21, TP27, TP28: S2761-46R; MPN S2761-46R
U12: TPS7A87; Texas-WQFN-20
U14, U17: INA186A1DD; SOT-23-8; MPN INA186A1IDDF
U15: TS5A3159ADBVR; SOT-23-6; MPN TS5A3159ADBVR
U16, U21: TS5A23159DGS; VSSOP-10_3x3mm_P0.5mm; MPN TS5A23159DGS
U20: MCP6V82; MSOP-8_3x3mm_P0.65mm; MPN MCP6V82-E/MS

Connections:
+5V: C32.2, C33.2, C41.1, C56.1, C74.1, U12.1 (IN1), U12.2 (IN1), U12.4 (IN2), U12.5 (IN2), U15.5 (V+), U16.8 (VCC), U21.8 (VCC); also elsewhere on the board
/Emulator/DBG_OUT: U21.2, U21.6; also elsewhere on the board
/Emulator/EM_OUT: R55.2, TP16.1, U16.2, U16.6; also elsewhere on the board
/Emulator/Emulator MCU/DBG_OUT_DIS_EN: U21.5; also elsewhere on the board
/Emulator/Emulator MCU/DBG_OUT_EN: U21.1; also elsewhere on the board
/Emulator/Emulator MCU/DBG_PSU_EN: U12.6 (EN2); also elsewhere on the board
/Emulator/Emulator MCU/DBG_PSU_PG: U12.9 (PG2); also elsewhere on the board
/Emulator/Emulator MCU/DGB_OUT_ADC: R63.2, R64.1, TP28.1; also elsewhere on the board
/Emulator/Emulator MCU/DGB_PSU_DAC: R62.2, TP27.1; also elsewhere on the board
/Emulator/Emulator MCU/EM_HIGH_CUR_ADC: R47.1, TP20.1; also elsewhere on the board
/Emulator/Emulator MCU/EM_LOW_CUR_ADC: R46.1, TP21.1; also elsewhere on the board
/Emulator/Emulator MCU/EM_LOW_RANGE_EN: U15.6; also elsewhere on the board
/Emulator/Emulator MCU/EM_OUT_ADC: C70.1, R44.2, TP14.1; also elsewhere on the board
/Emulator/Emulator MCU/EM_OUT_DIS_EN: U16.5; also elsewhere on the board
/Emulator/Emulator MCU/EM_OUT_EN: U16.1; also elsewhere on the board
/Emulator/Emulator MCU/EM_PSU_DAC: R33.2, TP19.1; also elsewhere on the board
/Emulator/Emulator MCU/EM_PSU_EN: U12.20 (EN1); also elsewhere on the board
/Emulator/Emulator MCU/EM_PSU_PG: U12.17 (PG1); also elsewhere on the board
GND: C32.1, C33.1, C34.1, C35.1, C36.1, C37.1, C38.1, C41.2, C52.2, C53.1, C54.2, C55.1, C56.2, C60.1, C61.1, C70.2, C71.2, C72.2, C73.1, C74.2, JP4.1, JP5.1, R26.1, R28.1, R32.1, R42.2, R56.1, R58.2, R61.1, R64.2, R65.2, U12.3 (GND), U12.13 (GND), U12.21 (PAD), U14.3 (REF), U14.4 (GND), U15.2 (GND), U16.3 (GND), U17.3 (REF), U17.4 (GND), U20.4 (V-), U21.3 (GND); also elsewhere on the board
unnamed: C36.2, C61.2, C66.2, R25.2, R37.2, R38.2, TP12.1, U12.14 (OUT1), U12.15 (OUT1)
unnamed: C37.2, C60.2, C65.2, R27.2, R63.1, TP11.1, U12.11 (OUT2), U12.12 (OUT2), U21.10
unnamed: C38.2, R31.2, R32.2, R33.1
unnamed: C73.2, R60.2, R61.2, R62.1
unnamed: R34.2, R35.2, U15.1
unnamed: R35.1, R36.2, R59.1, TP17.1, U15.3, U16.10
unnamed: R38.1, R41.2, TP15.1, U15.4
unnamed: R40.2, R57.2, U20.7
unnamed: R42.1, U16.4
unnamed: R44.1, R54.2, U20.1
unnamed: R46.2, U17.5
unnamed: R47.2, U14.5
unnamed: R65.1, U21.4
unnamed: C66.1, R25.1, R26.2, R31.1, R40.1, U12.16 (FB1)
unnamed: C34.2, U12.19 (NR/SS1)
unnamed: JP4.2, U12.18 (SS_CTRL1)
unnamed: C65.1, R27.1, R28.2, R60.1, U12.10 (FB2)
unnamed: C35.2, U12.7 (NR/SS2)
unnamed: JP5.2, U12.8 (SS_CTRL2)
unnamed: C40.2, R37.1, U14.7 (+)
unnamed: C40.1, R41.1, U14.8 (-)
unnamed: C39.2, R34.1, U17.7 (+)
unnamed: C39.1, R36.1, U17.8 (-)
unnamed: R55.1, R56.2, U20.3 (+)
unnamed: R54.1, U20.2 (-)
unnamed: R58.1, R59.2, U20.5 (+)
unnamed: R57.1, U20.6 (-)
VDDA: C52.1, C53.2, C54.1, C55.2, C71.1, C72.1, U14.1 (V+), U14.2 (EN), U17.1 (V+), U17.2 (EN), U20.8 (V+); also elsewhere on the board

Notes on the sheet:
0.5 * divider 5v -> 2.5v
DGB TAKEOVER PSU
VARIABLE PSU
RSENSE
